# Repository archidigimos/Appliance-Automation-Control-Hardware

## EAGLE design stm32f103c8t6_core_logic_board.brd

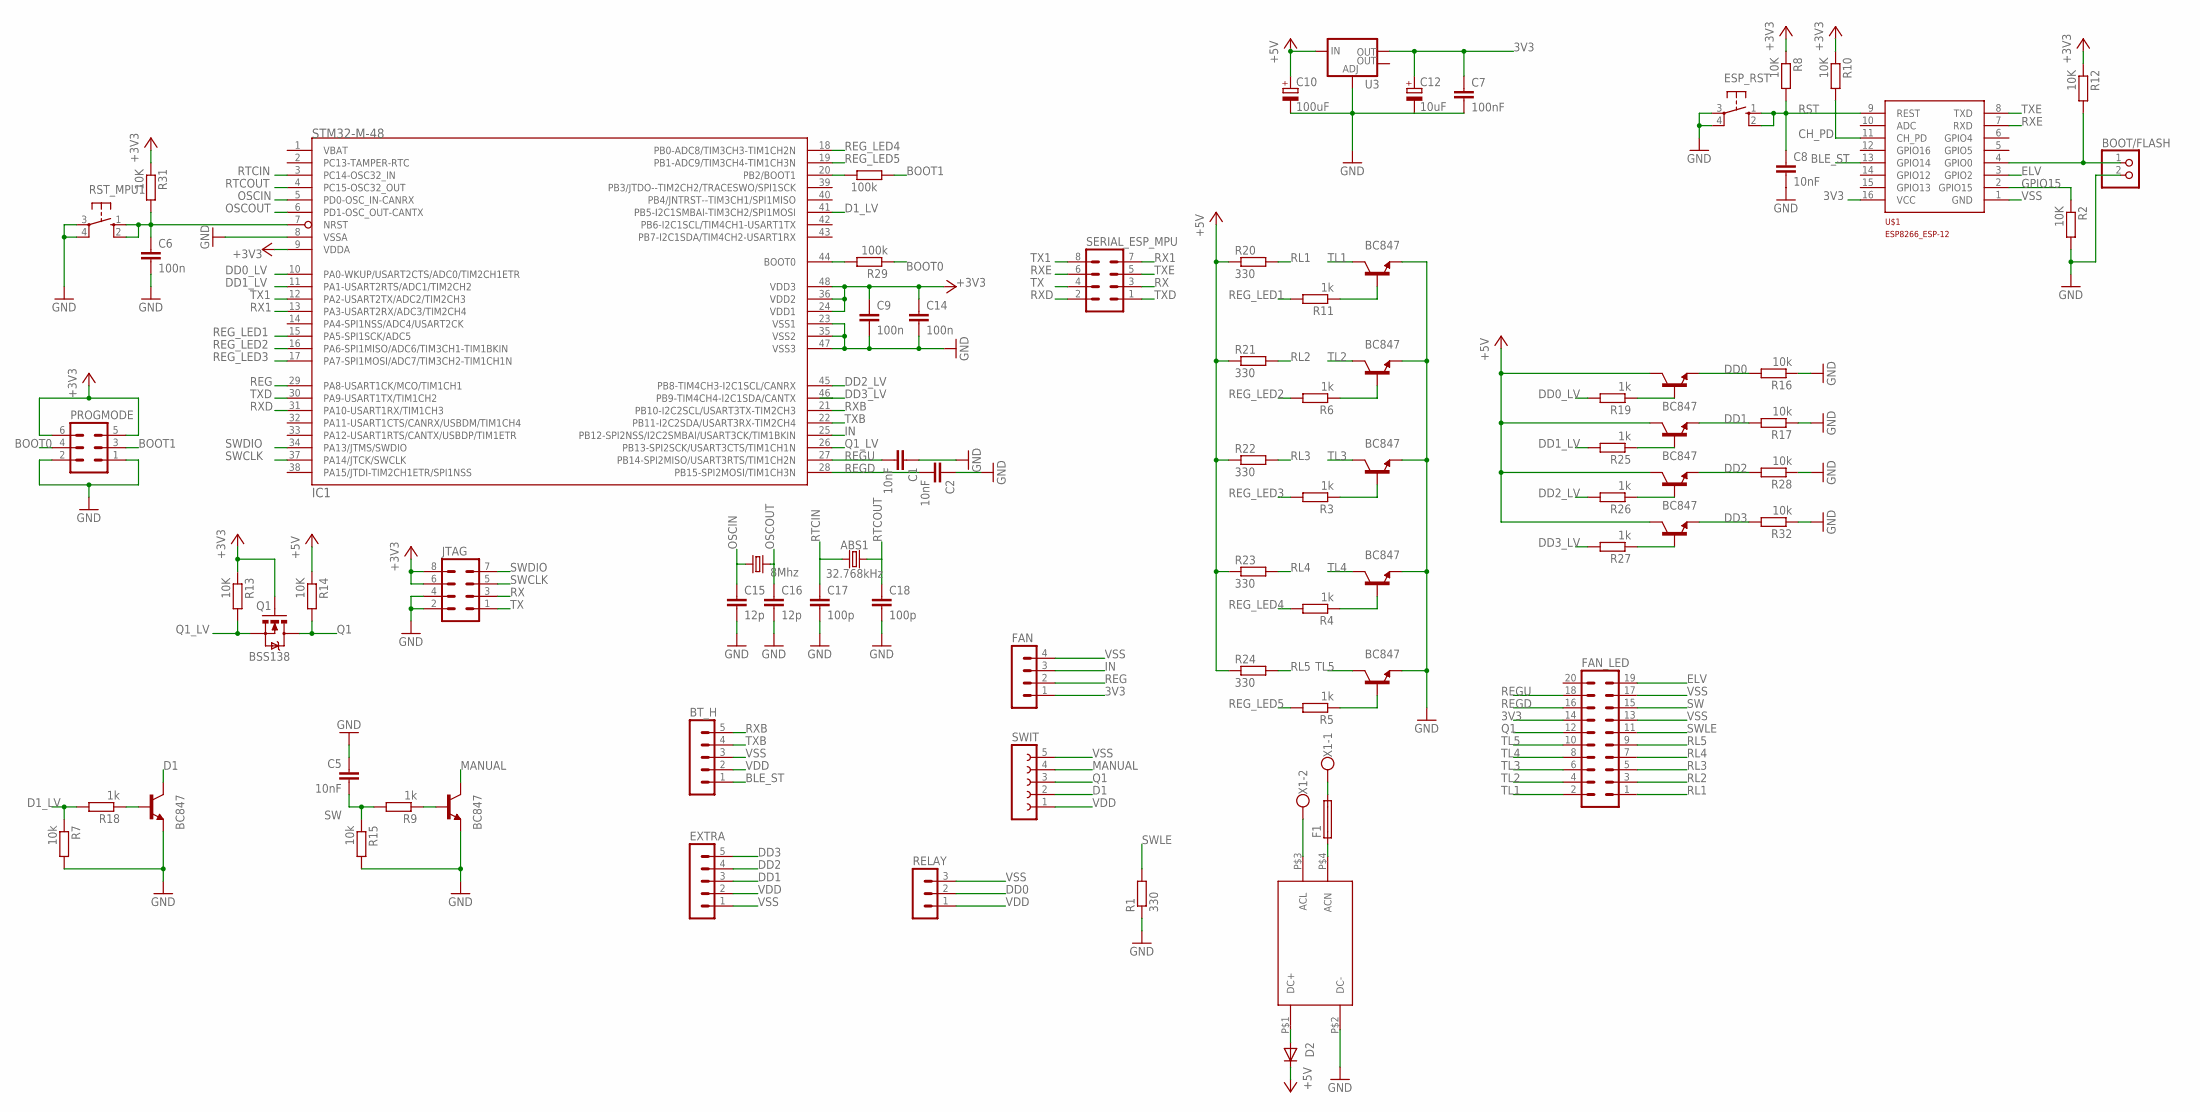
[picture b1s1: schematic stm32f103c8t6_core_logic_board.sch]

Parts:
ABS1: 32.768kHz; CRYSTAL-PTH-2X6-CYL
BOOT/FLASH: PINHD-1X2; 1X02
BT_H: MA05-1
C1, C2, C5, C8: 10nF; C1206
C6, C9, C14: 100n; C1206
C7: 100nF; C1206
C10: 100uF; 153CLV-0605
C12: 10uF; 153CLV-0405
C15, C16: 12p; C1206
C17, C18: 100p; C1206
D1_C, D1_C1: BC847; SOT23
D2: 1N4004; DO41-10
DD0_C, DD1_C, DD2_C, DD3_C: BC847; SOT23
ESP_RST: 10-XX; B3F-10XX
EXTRA: MA05-1
F1: SH22,5A
FAN: MA04-1
FAN_LED: MA10-2
IC1: STM32-M-48; LQFP48
JTAG: MA04-2
L1, L2, L3, L4, L5: BC847; SOT23
PROGMODE: MA03-2
Q1: BSS138; SOT23-3
Q2: 8Mhz; HC49U-V
R1, R20, R21, R22, R23, R24: 330; R1206
R2, R8, R10, R12, R13, R14, R31: 10K; R1206
R3, R4, R5, R6, R9, R11, R18, R19, R25, R26, R27: 1k; M1206
R7, R15, R16, R17, R28, R32: 10k; M1206
R29, R30: 100k; R1206
RELAY: MA03-1
RST_MPU1: 10-XX; B3F-10XX
SERIAL_ESP_MPU: MA04-2
SWIT: FE05-1
U3: V_REG_LM1117SOT223; SOT223
U$1: ESP8266_ESP-12; ESP8266-ESP12
U$2: SDOWN_POWER_SUPPLYPOWER_SUPPLY; SDOWN_POWER_SUPPLY
X1: W237-102

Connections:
3V3: C7.1, C9.1, C12.+, C14.1, FAN.1, FAN_LED.14, IC1.9 (VDDA), IC1.24 (VDD1), IC1.36 (VDD2), IC1.48 (VDD3), JTAG.6, JTAG.8, PROGMODE.5, PROGMODE.6, Q1.1 (G), R8.1, R10.1, R12.1, R13.1, R31.1, U3.2 (OUT), U$1.16 (VCC)
BLE_ST: BT_H.1, U$1.13 (GPIO14)
BOOT0: PROGMODE.4, R29.1
BOOT1: PROGMODE.3, R30.2
CH_PD: R10.2, U$1.11 (CH_PD)
D1: D1_C.3 (C), SWIT.2
D1_LV: IC1.41 (PB5-I2C1SMBAI-TIM3CH2/SPI1MOSI), R7.1, R18.2
DD0: DD0_C.2 (E), R16.2, RELAY.2
DD0_LV: IC1.10 (PA0-WKUP/USART2CTS/ADC0/TIM2CH1ETR), R19.2
DD1: DD1_C.2 (E), EXTRA.3, R17.2
DD1_LV: IC1.11 (PA1-USART2RTS/ADC1/TIM2CH2), R25.2
DD2: DD2_C.2 (E), EXTRA.4, R28.2
DD2_LV: IC1.45 (PB8-TIM4CH3-I2C1SCL/CANRX), R26.2
DD3: DD3_C.2 (E), EXTRA.5, R32.2
DD3_LV: IC1.46 (PB9-TIM4CH4-I2C1SDA/CANTX), R27.2
ELV: FAN_LED.19, U$1.3 (GPIO2)
GPIO0: BOOT/FLASH.1, R12.2, U$1.4 (GPIO0)
GPIO15: R2.1, U$1.2 (GPIO15)
IN: FAN.3, IC1.25 (PB12-SPI2NSS/I2C2SMBAI/USART3CK/TIM1BKIN)
MANUAL: D1_C1.3 (C), SWIT.4
unnamed: L1.1 (B), R11.1
unnamed: IC1.44 (BOOT0), R29.2
unnamed: L2.1 (B), R6.1
unnamed: L3.1 (B), R3.1
unnamed: D2.A, U$2.P$1 (DC+)
unnamed: L4.1 (B), R4.1
unnamed: L5.1 (B), R5.1
unnamed: F1.2, X1.1
unnamed: F1.1, U$2.P$4 (ACN)
unnamed: U$2.P$3 (ACL), X1.2
unnamed: D1_C.1 (B), R18.1
unnamed: IC1.20 (PB2/BOOT1), R30.1
unnamed: D1_C1.1 (B), R9.1
unnamed: DD0_C.1 (B), R19.1
unnamed: DD1_C.1 (B), R25.1
unnamed: DD2_C.1 (B), R26.1
unnamed: DD3_C.1 (B), R27.1
OSCIN: C15.1, IC1.5 (PD0-OSC_IN-CANRX), Q2.1
OSCOUT: C16.1, IC1.6 (PD1-OSC_OUT-CANTX), Q2.2
Q1: FAN_LED.12, Q1.3 (D), R14.2, SWIT.3
Q1_LV: IC1.26 (PB13-SPI2SCK/USART3CTS/TIM1CH1N), Q1.2 (S), R13.2
REG: FAN.2, IC1.29 (PA8-USART1CK/MCO/TIM1CH1)
REGD: C2.2, FAN_LED.16, IC1.28 (PB15-SPI2MOSI/TIM1CH3N)
REGU: C1.2, FAN_LED.18, IC1.27 (PB14-SPI2MISO/USART3RTS/TIM1CH2N)
REG_LED1: IC1.15 (PA5-SPI1SCK/ADC5), R11.2
REG_LED2: IC1.16 (PA6-SPI1MISO/ADC6/TIM3CH1-TIM1BKIN), R6.2
REG_LED3: IC1.17 (PA7-SPI1MOSI/ADC7/TIM3CH2-TIM1CH1N), R3.2
REG_LED4: IC1.18 (PB0-ADC8/TIM3CH3-TIM1CH2N), R4.2
REG_LED5: IC1.19 (PB1-ADC9/TIM3CH4-TIM1CH3N), R5.2
RESET1: C6.1, IC1.7 (NRST), R31.2, RST_MPU1.1 (S), RST_MPU1.2 (S1)
RL1: FAN_LED.1, R20.2
RL2: FAN_LED.3, R21.2
RL3: FAN_LED.5, R22.2
RL4: FAN_LED.7, R23.2
RL5: FAN_LED.9, R24.2
RST: C8.1, ESP_RST.1 (S), ESP_RST.2 (S1), R8.2, U$1.9 (REST)
RTCIN: ABS1.1, C17.1, IC1.3 (PC14-OSC32_IN)
RTCOUT: ABS1.2, C18.1, IC1.4 (PC15-OSC32_OUT)
RX: JTAG.3, SERIAL_ESP_MPU.3
RX1: IC1.13 (PA3-USART2RX/ADC3/TIM2CH4), SERIAL_ESP_MPU.7
RXB: BT_H.5, IC1.21 (PB10-I2C2SCL/USART3TX-TIM2CH3)
RXD: IC1.31 (PA10-USART1RX/TIM1CH3), SERIAL_ESP_MPU.2
RXE: SERIAL_ESP_MPU.6, U$1.7 (RXD)
SW: C5.2, FAN_LED.15, R9.2, R15.1
SWCLK: IC1.37 (PA14/JTCK/SWCLK), JTAG.5
SWDIO: IC1.34 (PA13/JTMS/SWDIO), JTAG.7
SWLE: FAN_LED.11, R1.2
TL1: FAN_LED.2, L1.3 (C)
TL2: FAN_LED.4, L2.3 (C)
TL3: FAN_LED.6, L3.3 (C)
TL4: FAN_LED.8, L4.3 (C)
TL5: FAN_LED.10, L5.3 (C)
TX: JTAG.1, SERIAL_ESP_MPU.4
TX1: IC1.12 (PA2-USART2TX/ADC2/TIM2CH3), SERIAL_ESP_MPU.8
TXB: BT_H.4, IC1.22 (PB11-I2C2SDA/USART3RX-TIM2CH4)
TXD: IC1.30 (PA9-USART1TX/TIM1CH2), SERIAL_ESP_MPU.1
TXE: SERIAL_ESP_MPU.5, U$1.8 (TXD)
VDD: BT_H.2, C10.+, D2.C, DD0_C.3 (C), DD1_C.3 (C), DD2_C.3 (C), DD3_C.3 (C), EXTRA.2, R14.1, R20.1, R21.1, R22.1, R23.1, R24.1, RELAY.1, SWIT.1, U3.3 (IN)
VSS: BOOT/FLASH.2, BT_H.3, C1.1, C2.1, C5.1, C6.2, C7.2, C8.2, C9.2, C10.-, C12.-, C14.2, C15.2, C16.2, C17.2, C18.2, D1_C.2 (E), D1_C1.2 (E), ESP_RST.3, ESP_RST.4 (P1), EXTRA.1, FAN.4, FAN_LED.13, FAN_LED.17, IC1.8 (VSSA), IC1.23 (VSS1), IC1.35 (VSS2), IC1.47 (VSS3), JTAG.2, JTAG.4, L1.2 (E), L2.2 (E), L3.2 (E), L4.2 (E), L5.2 (E), PROGMODE.1, PROGMODE.2, R1.1, R2.2, R7.2, R15.2, R16.1, R17.1, R28.1, R32.1, RELAY.3, RST_MPU1.3, RST_MPU1.4 (P1), SWIT.5, U3.1 (ADJ), U$1.1 (GND), U$2.P$2 (DC-)

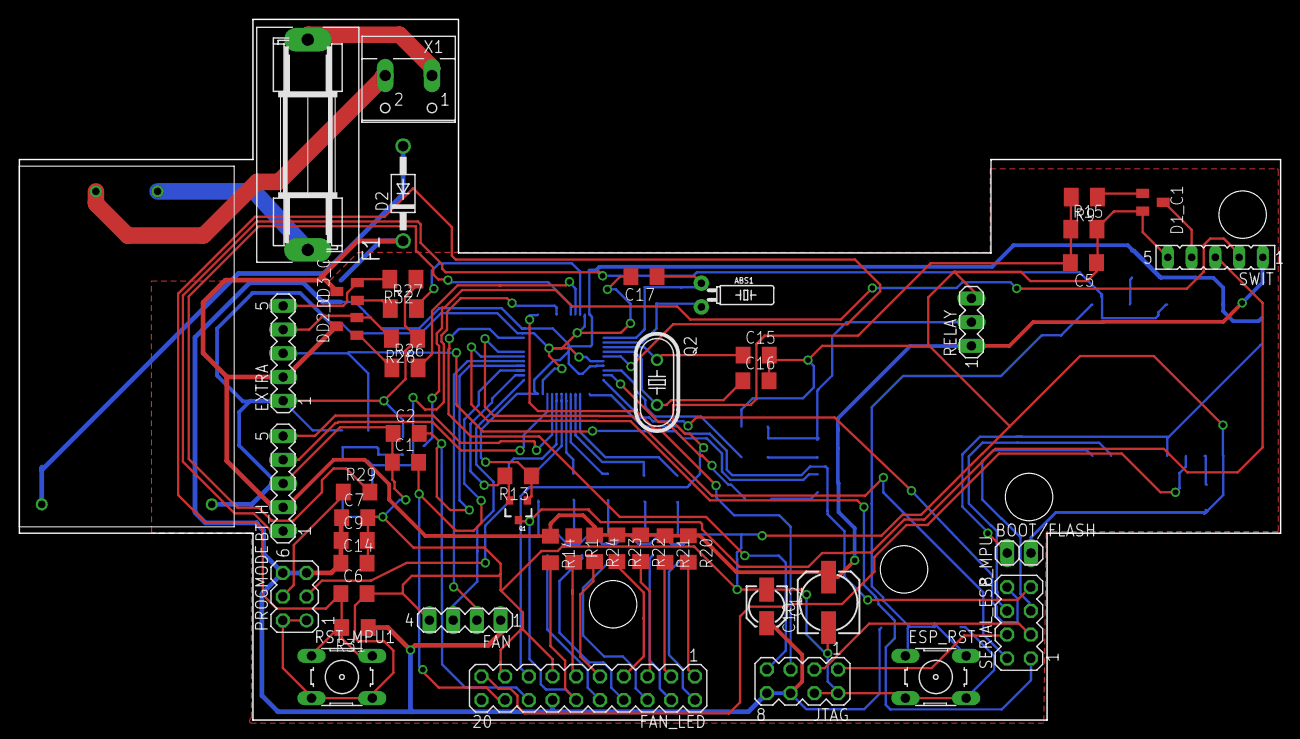
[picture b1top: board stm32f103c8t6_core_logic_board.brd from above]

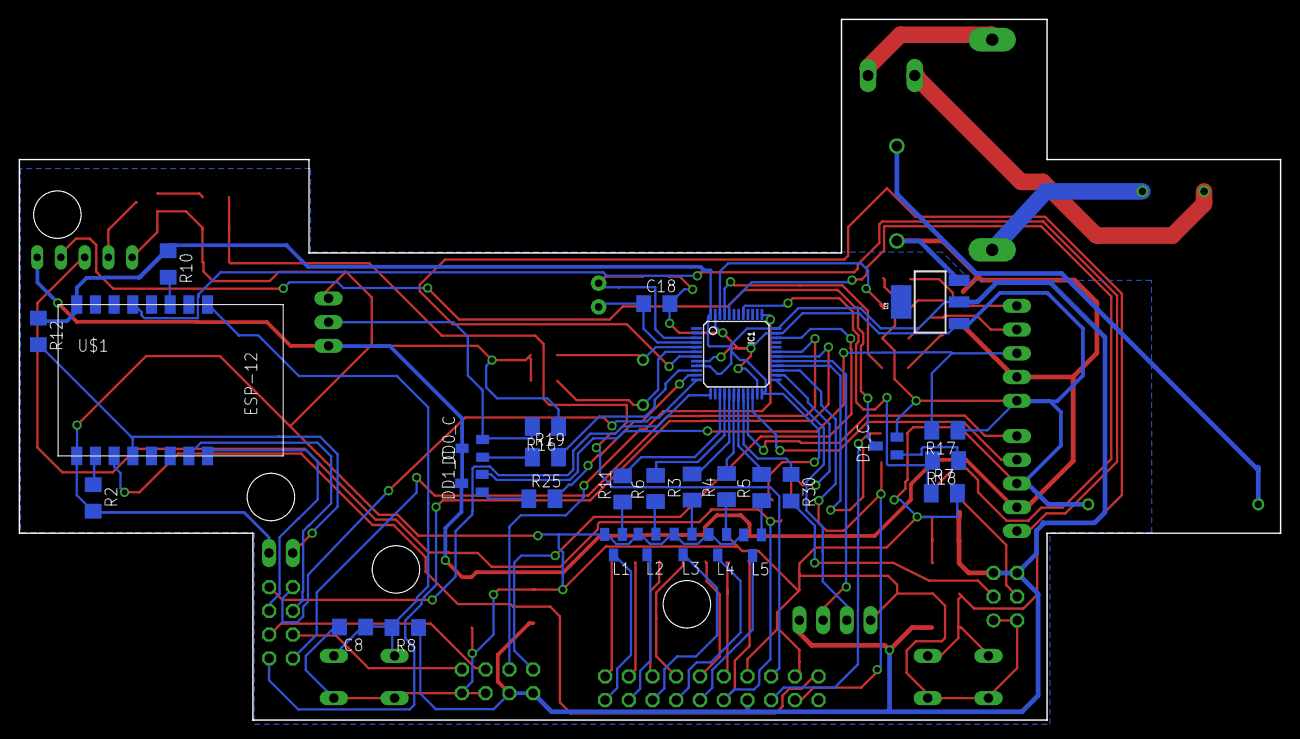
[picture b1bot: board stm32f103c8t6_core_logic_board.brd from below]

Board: 2 copper layers, 135.0 x 75.0 mm, 79 parts (29 on the bottom side), 79 nets.

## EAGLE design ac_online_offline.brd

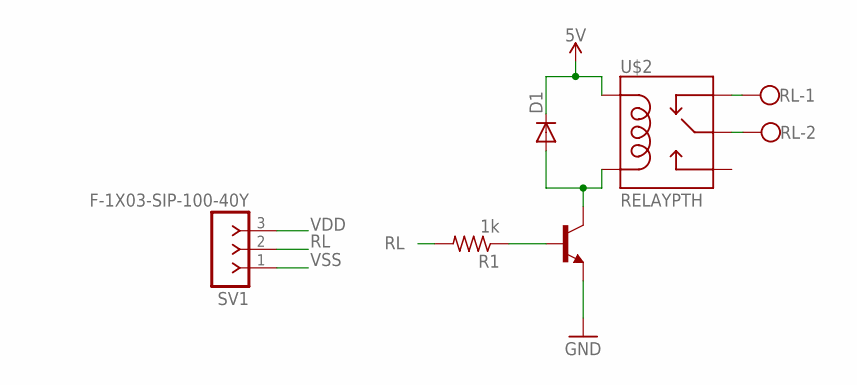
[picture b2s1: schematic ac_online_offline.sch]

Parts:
D1: 1N4148DO35-7; DO35-7
R1: 1k; M1206
RL: W237-102
SV1: F-1X03-SIP-100-40Y; SIP-100-03-40Y
T1: BC847; SOT23
U$2: RELAYPTH; SRD-05VDC-SL-C

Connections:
unnamed: RL.2, U$2.SWCOMMON
unnamed: RL.1, U$2.SWCLOSED (SWCLOSE)
unnamed: D1.A, T1.3 (C), U$2.COIL0
unnamed: R1.1, T1.1 (B)
RL: R1.2, SV1.2
VDD: D1.C, SV1.3, U$2.COIL1
VSS: SV1.1, T1.2 (E)

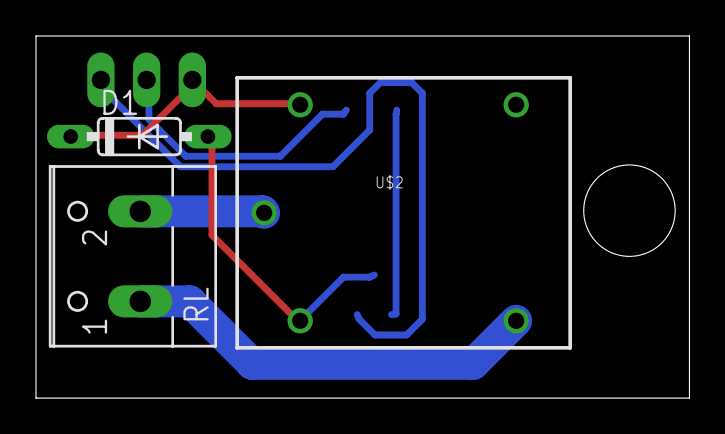
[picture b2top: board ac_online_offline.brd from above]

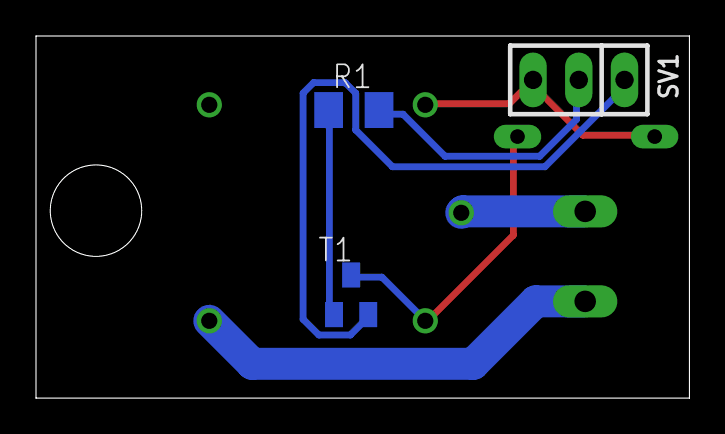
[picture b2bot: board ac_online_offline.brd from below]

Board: 2 copper layers, 36.3 x 20.1 mm, 6 parts (3 on the bottom side), 7 nets.

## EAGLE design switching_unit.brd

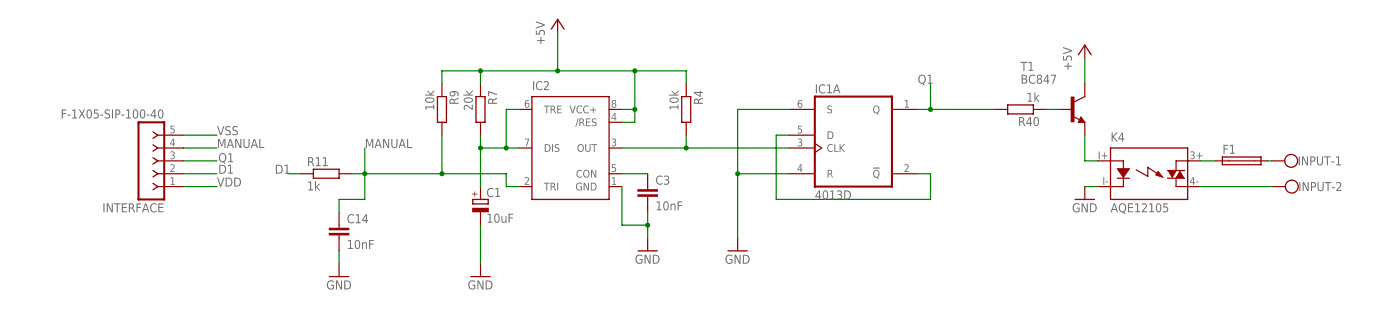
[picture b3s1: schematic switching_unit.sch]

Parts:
C1: 10uF; 153CLV-0405
C3, C14: 10nF; C1206
F1: SH22,5A
IC1: 4013D; SO14
IC2: NE555D; SO08
INPUT: W237-102
INTERFACE: F-1X05-SIP-100-40; SIP-100-05-40
K4: AQE12105; AQE
R4, R9: 10k; R1206
R7: 20k; R1206
R11, R40: 1k; R1206
T1: BC847; SOT23

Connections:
D1: INTERFACE.2, R11.1
MANUAL: C14.1, IC2.2 (TRI), INTERFACE.4, R9.2, R11.2
unnamed: R40.1, T1.1 (B)
unnamed: INPUT.2, K4.4- (DS2)
unnamed: F1.2, INPUT.1
unnamed: K4.I+ (A), T1.2 (E)
unnamed: IC1.2 (!Q), IC1.5 (D)
unnamed: IC1.3 (CLK), IC2.3 (OUT), R4.2
unnamed: C1.+, IC2.6 (TRE), IC2.7 (DIS), R7.2
unnamed: C3.1, IC2.5 (CON)
unnamed: F1.1, K4.3+ (DS1)
Q1: IC1.1 (Q), INTERFACE.3, R40.2
VDD: IC1.14 (VDD), IC2.4 (/RES), IC2.8 (VCC+), INTERFACE.1, R4.1, R7.1, R9.1, T1.3 (C)
VSS: C1.-, C3.2, C14.2, IC1.4 (R), IC1.6 (S), IC1.7 (VSS), IC2.1 (GND), INTERFACE.5, K4.I- (K)

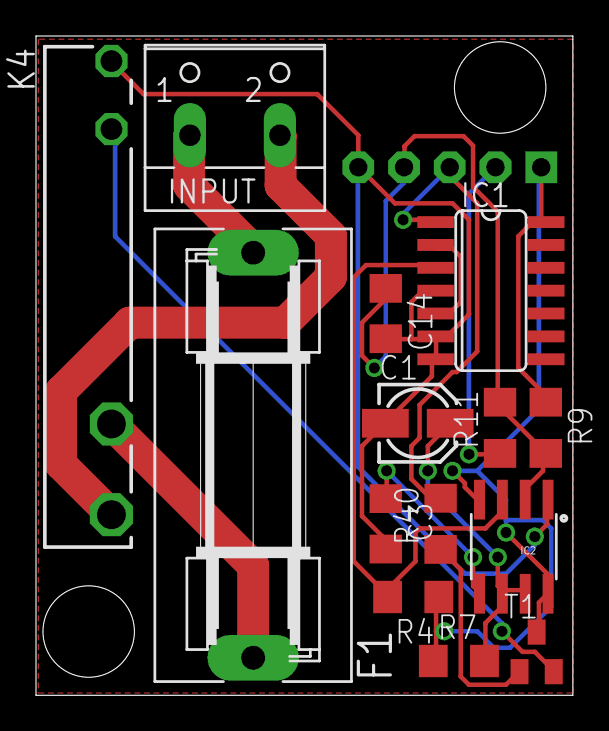
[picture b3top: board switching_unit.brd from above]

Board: 2 copper layers, 29.8 x 36.6 mm, 15 parts (1 on the bottom side), 14 nets.

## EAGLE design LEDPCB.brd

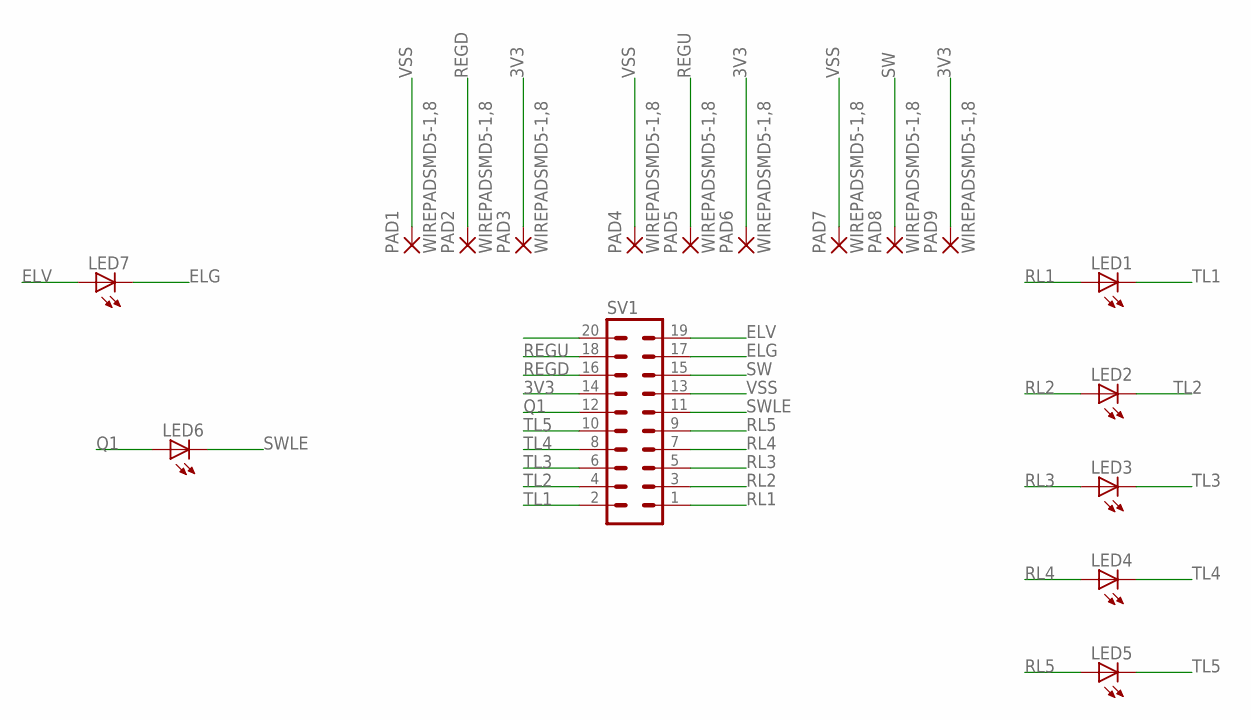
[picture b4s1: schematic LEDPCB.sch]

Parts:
LED1, LED2, LED3, LED4, LED5, LED6, LED7: LEDSMT1206; 1206
PAD1, PAD2, PAD3, PAD4, PAD5, PAD6, PAD7, PAD8, PAD9: WIREPADSMD5-1,8; 5-1,8
SV1: MA10-2

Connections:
3V3: PAD3.1, PAD6.1, PAD9.1, SV1.14
ELG: LED7.C, SV1.17
ELV: LED7.A, SV1.19
Q1: LED6.A, SV1.12
REGD: PAD2.1, SV1.16
REGU: PAD5.1, SV1.18
RL1: LED1.A, SV1.1
RL2: LED2.A, SV1.3
RL3: LED3.A, SV1.5
RL4: LED4.A, SV1.7
RL5: LED5.A, SV1.9
SW: PAD8.1, SV1.15
SWLE: LED6.C, SV1.11
TL1: LED1.C, SV1.2
TL2: LED2.C, SV1.4
TL3: LED3.C, SV1.6
TL4: LED4.C, SV1.8
TL5: LED5.C, SV1.10
VSS: PAD1.1, PAD4.1, PAD7.1, SV1.13

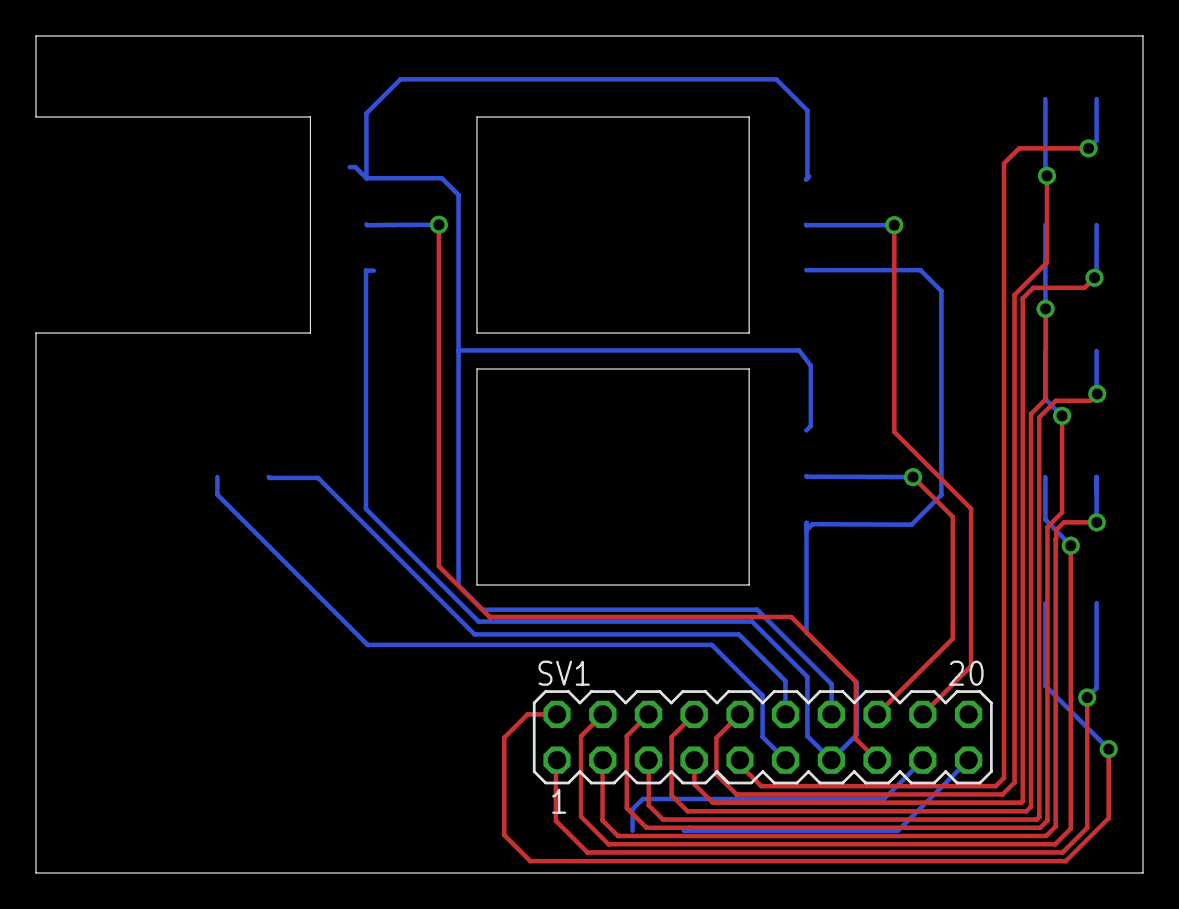
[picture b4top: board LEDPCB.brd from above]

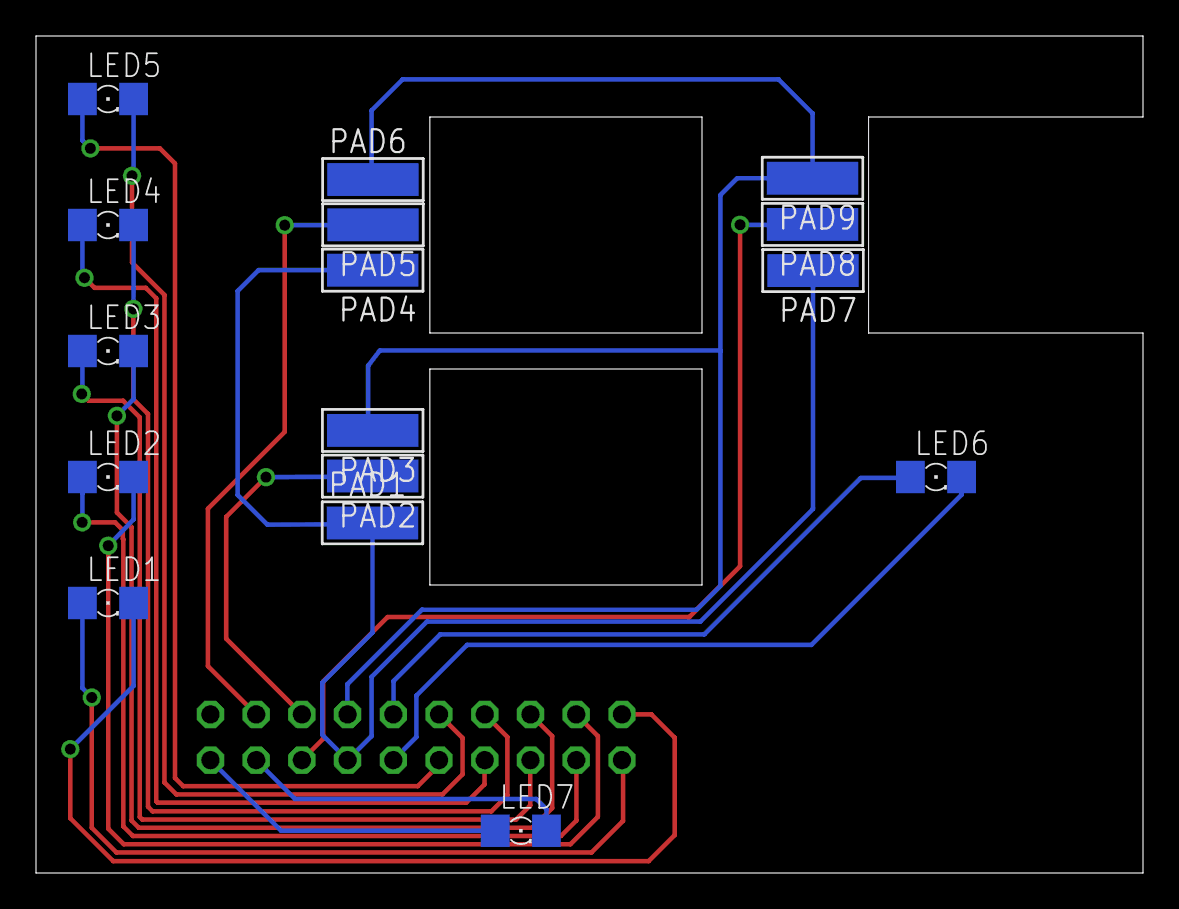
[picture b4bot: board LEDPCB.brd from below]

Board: 2 copper layers, 61.5 x 46.5 mm, 17 parts (16 on the bottom side), 19 nets.

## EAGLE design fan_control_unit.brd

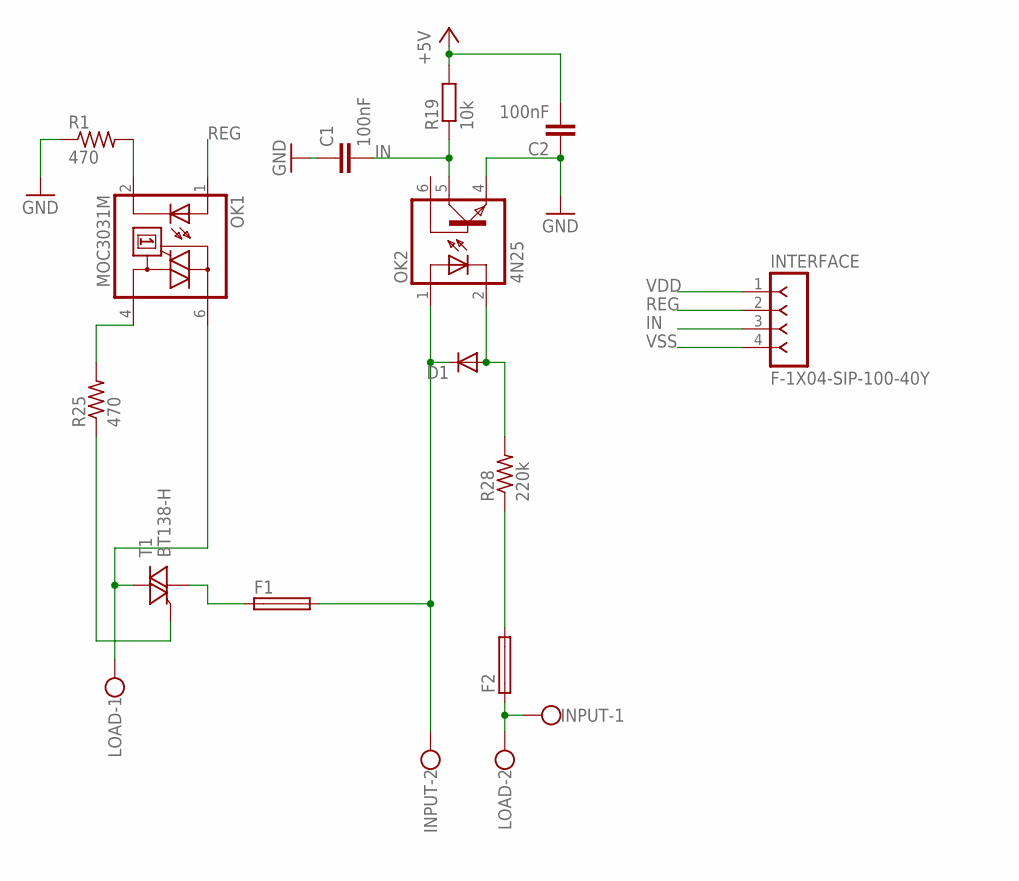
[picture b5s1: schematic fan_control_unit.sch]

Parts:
C1, C2: 100nF; C1206
D1: 1N4148DO35-7; DO35-7
F1, F2: SH22,5A
INPUT: W237-102
INTERFACE: F-1X04-SIP-100-40Y; SIP-100-04-40Y
LOAD: W237-102
OK1: MOC3031M; DIL06
OK2: 4N25; DIL06
R1, R25: 470; 0207/15
R19: 10k; R1206
R28: 220k; 0207/15
T1: BT138-H; TO220BH

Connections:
GATE: R25.1, T1.G
IN: C1.2, INTERFACE.3, OK2.5 (COL), R19.1
unnamed: F1.1, T1.T1 (A1)
unnamed: F2.2, R28.1
unnamed: F2.1, INPUT.1, LOAD.2
unnamed: OK1.4 (A1), R25.2
unnamed: OK1.2 (C), R1.2
unnamed: D1.A, OK2.2 (C), R28.2
unnamed: LOAD.1, OK1.6 (A2), T1.T2 (A2)
unnamed: D1.C, F1.2, INPUT.2, OK2.1 (A)
REG: INTERFACE.2, OK1.1 (A)
VDD: C2.2, INTERFACE.1, R19.2
VSS: C1.1, C2.1, INTERFACE.4, OK2.4 (EMI), R1.1

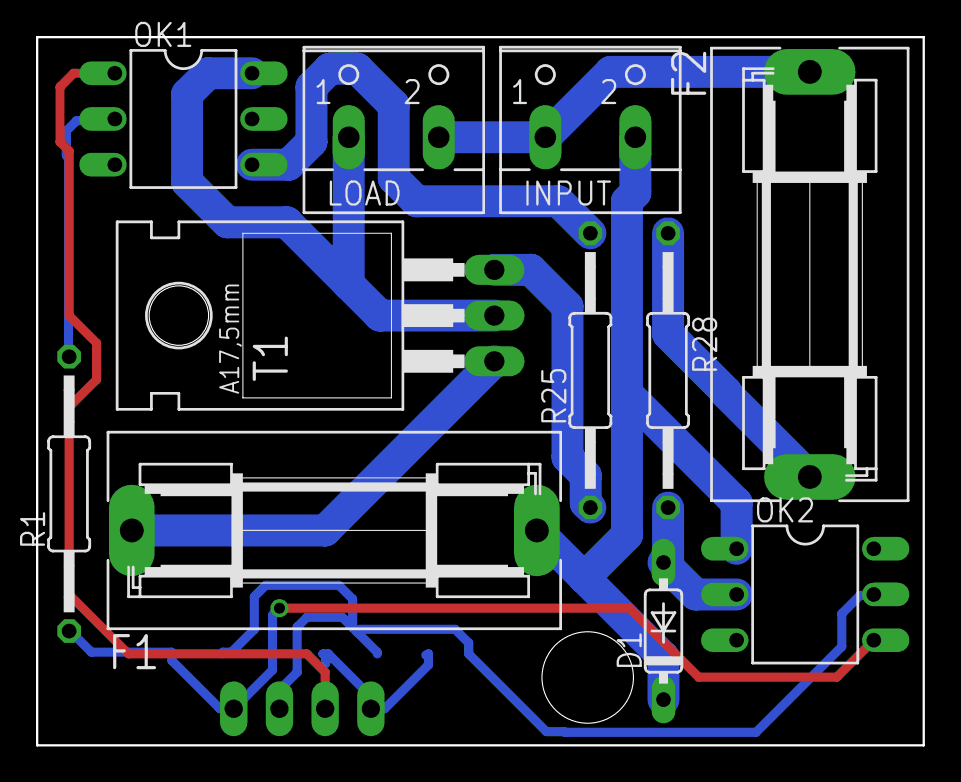
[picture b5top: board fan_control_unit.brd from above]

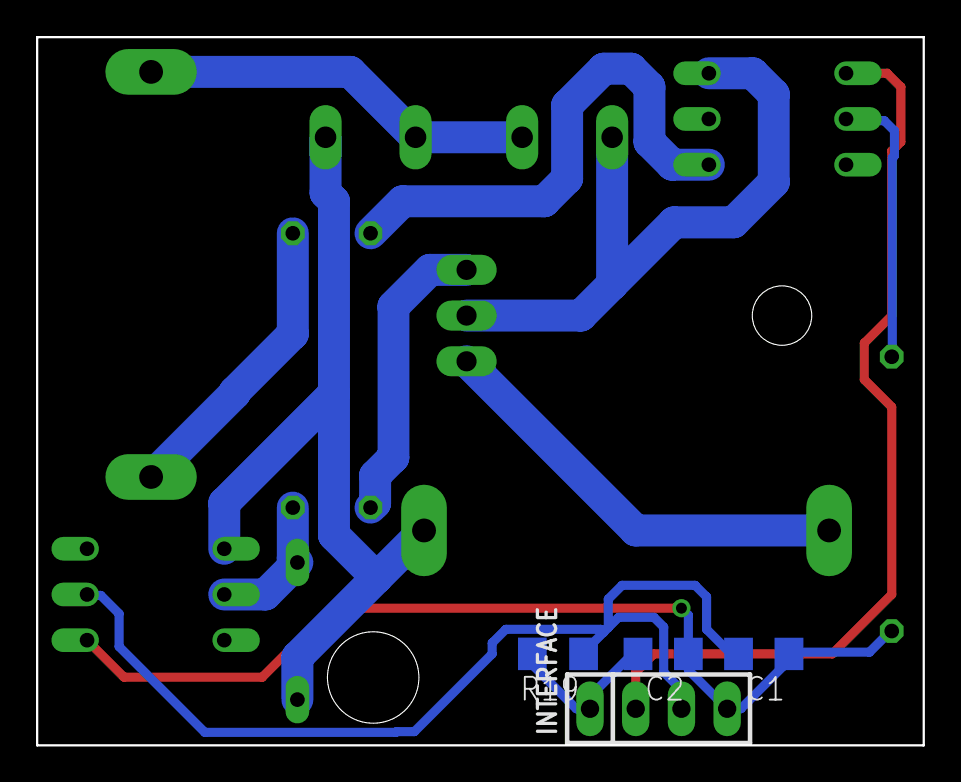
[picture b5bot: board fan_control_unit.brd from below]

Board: 2 copper layers, 49.3 x 39.3 mm, 15 parts (4 on the bottom side), 13 nets.

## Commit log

2017-09-28 :tada: Added .gitattributes & .gitignore files
2017-09-28 Appliance Automation Control Hardware

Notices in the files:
parts and their libraries:
con-headers-jp: Copyright (C) 2008, Bob Starr
SparkFun-PowerSymbols: Licensing: Creative Commons ShareAlike 4.0 International - https://creativecommons.org/licenses/by-sa/4.0
